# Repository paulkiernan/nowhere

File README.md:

# NowHere

> The difference between nowhere and now here is a little space

[Indiegogo Campaign](https://www.indiegogo.com/projects/nowhere-burning-man-2019#/)

## Development

We use Docker to standardize our build environment. This minimizes uncertainty
around cross-complilation by giving us identical base environments and also
keeps out host environments clean. Currently (2019-06-13) we build for the
Ubuntu Bionic (LTS) target via the DockerFile in the root of this repo.

### Mac Setup

The Teensy loader runs in a X11 window so we need to install XQuartz for flashing
to work on Mac.

```
brew cask install docker
```

* Activate the option ‘Allow connections from network clients’ in XQuartz settings
* Quit & restart XQuartz (to activate the setting)

### Linux Setup

Ubuntu and other modern Linux distibutions use udev to manage device files when
USB devices are added and removed. By default, udev will create a device with
read-only permission which will not allow to you download code. You must place
the udev rules file at /etc/udev/rules.d/49-teensy.rules

```
curl -L https://www.pjrc.com/teensy/49-teensy.rules > /etc/udev/rules.d/49-teensy.rules
```

```bash
./develop
make
make upload
```

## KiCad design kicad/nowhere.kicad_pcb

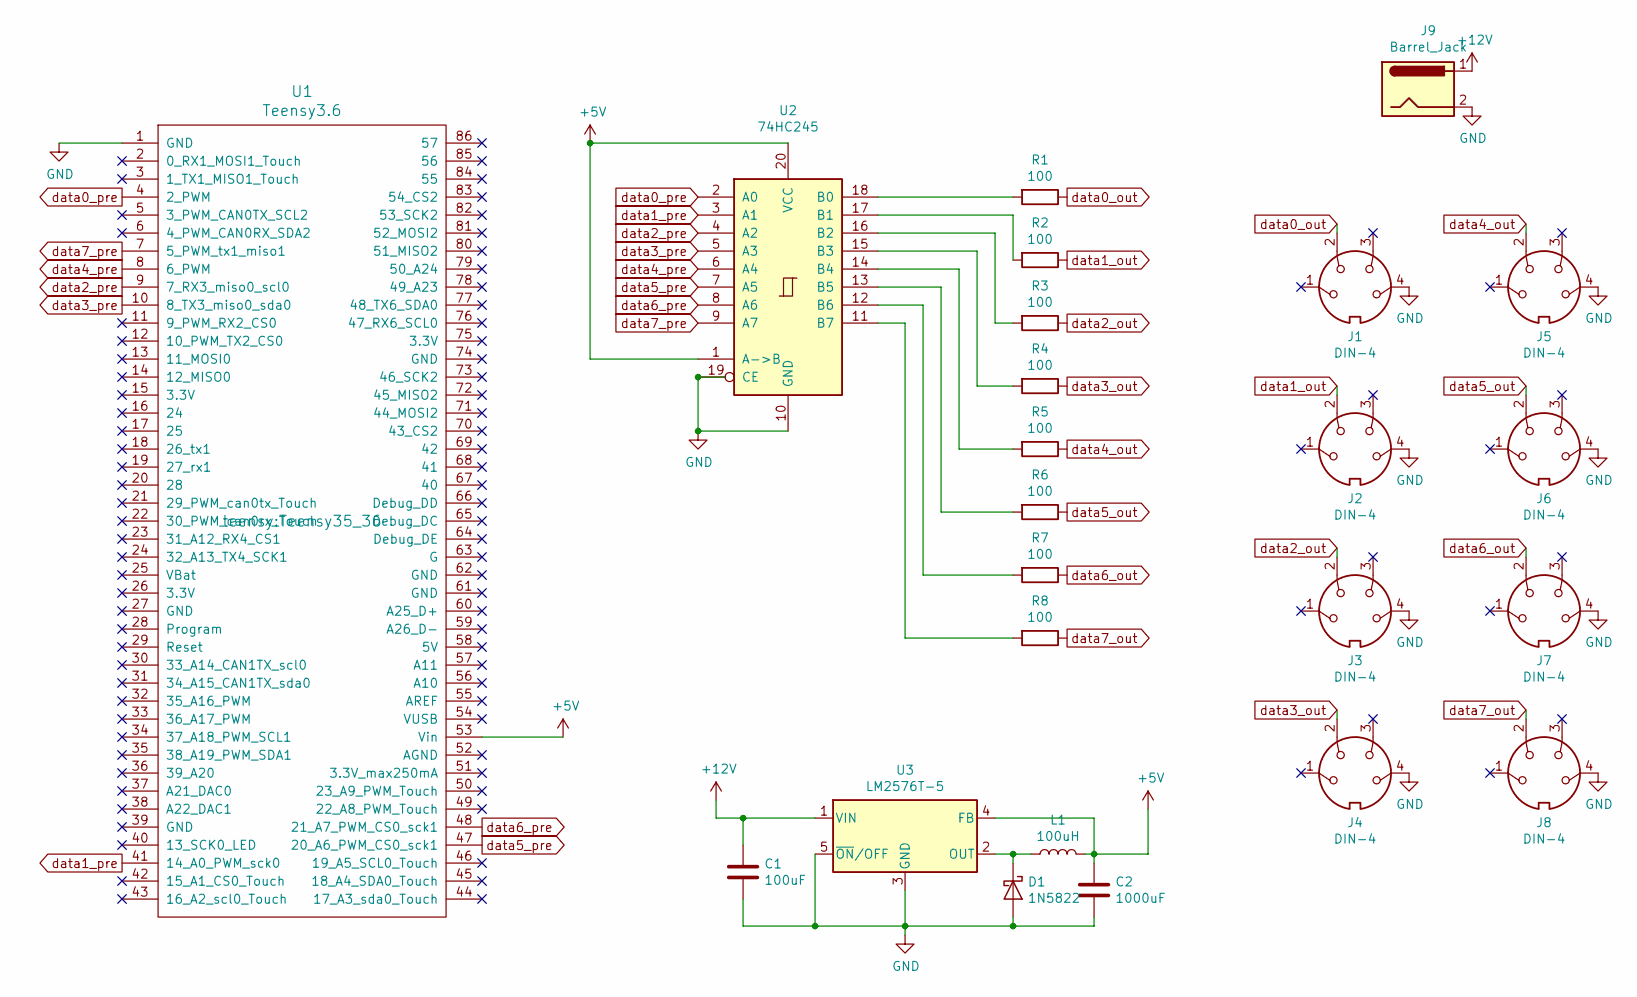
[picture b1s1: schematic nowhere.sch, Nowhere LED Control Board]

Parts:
C1: 100uF; CP_Radial_D8.0mm_P3.50mm
C2: 1000uF; CP_Radial_D12.5mm_P5.00mm
D1: 1N5822; D_DO-201AD_P15.24mm_Horizontal
J1, J2, J3, J4, J5, J6, J7, J8: DIN-4; Molex_Nano-Fit_105310-xx04_2x02_P2.50mm_Vertical
J9: Barrel_Jack; BarrelJack_CUI_PJ-063AH_Horizontal
L1: 100uH; L_Radial_D12.0mm_P6.00mm_MuRATA_1900R
R1, R2, R3, R4, R5, R6, R7, R8: 100; R_Axial_DIN0207_L6.3mm_D2.5mm_P10.16mm_Horizontal
U1: Teensy3.6; Teensy35_36
U2: 74HC245; DIP-20_W7.62mm
U3: LM2576T-5; TO-220-5_Vertical

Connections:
+5V: C2.1, L1.2, U1.53 (Vin), U2.1 (A->B), U2.20 (VCC), U3.4 (FB)
+12V: C1.1, J1.1, J2.1, J3.1, J4.1, J5.1, J6.1, J7.1, J8.1, J9.1, U3.1 (VIN)
GND: C1.2, C2.2, D1.2 (A), J1.4, J2.4, J3.4, J4.4, J5.4, J6.4, J7.4, J8.4, J9.2, U1.1 (GND), U2.10 (GND), U2.19 (CE), U3.3 (GND), U3.5 (~ON~/OFF)
unnamed: D1.1 (K), L1.1, U3.2 (OUT)
unnamed: R1.2, U2.18 (B0)
unnamed: R2.2, U2.17 (B1)
unnamed: R3.2, U2.16 (B2)
unnamed: R4.2, U2.15 (B3)
unnamed: R5.2, U2.14 (B4)
unnamed: R6.2, U2.13 (B5)
unnamed: R7.2, U2.12 (B6)
unnamed: R8.2, U2.11 (B7)
data0_out: J1.2, R1.1
data0_pre: U1.4 (2_PWM), U2.2 (A0)
data1_out: J2.2, R2.1
data1_pre: U1.41 (14_A0_PWM_sck0), U2.3 (A1)
data2_out: J3.2, R3.1
data2_pre: U1.9 (7_RX3_miso0_scl0), U2.4 (A2)
data3_out: J4.2, R4.1
data3_pre: U1.10 (8_TX3_miso0_sda0), U2.5 (A3)
data4_out: J5.2, R5.1
data4_pre: U1.8 (6_PWM), U2.6 (A4)
data5_out: J6.2, R6.1
data5_pre: U1.47 (20_A6_PWM_CS0_sck1), U2.7 (A5)
data6_out: J7.2, R7.1
data6_pre: U1.48 (21_A7_PWM_CS0_sck1), U2.8 (A6)
data7_out: J8.2, R8.1
data7_pre: U1.7 (5_PWM_tx1_miso1), U2.9 (A7)

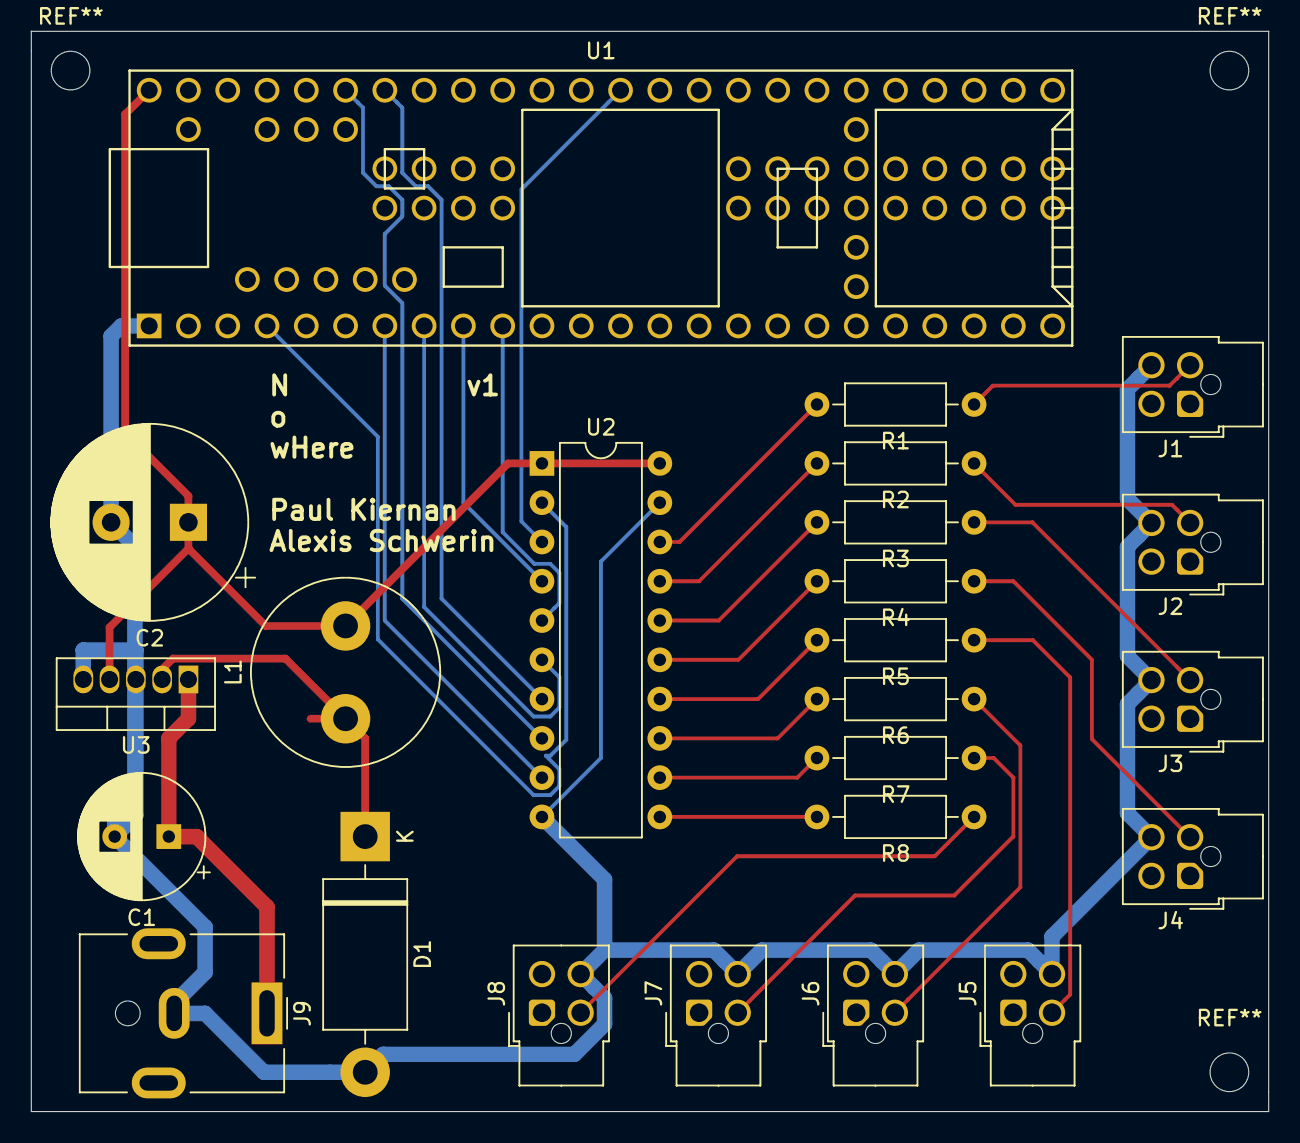
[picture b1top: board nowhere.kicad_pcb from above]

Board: 2 copper layers, 80.0 x 69.8 mm, 24 parts (0 on the bottom side), 28 nets.

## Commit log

2019-05-31 Init circuit layout
2019-06-06 Add PCB, gerber, and drill files
2019-06-06 Add image and readme
2019-06-06 Update gitignore
2019-06-13 PCB version 2
2019-06-14 Adds docker teensy flash framework
2019-06-14 Forward UID and GUID to container
2019-06-14 Basic 8 channel test
2019-06-14 Fix strip 5 pin
2019-06-15 Rename license
2019-06-15 Rainbow swipe
2019-06-15 Forward X11 over IP for macs
2019-06-18 Basic flickering test
2019-06-21 Move makefiles into separate dir
2019-08-17 Bike lights
2020-12-20 [ImgBot] Optimize images
    /media/nowhere.jpg -- 328.01kb -> 293.50kb (10.52%)
